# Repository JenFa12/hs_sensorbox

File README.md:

# hs_sensorbox
This is a sensorbox for home assistant

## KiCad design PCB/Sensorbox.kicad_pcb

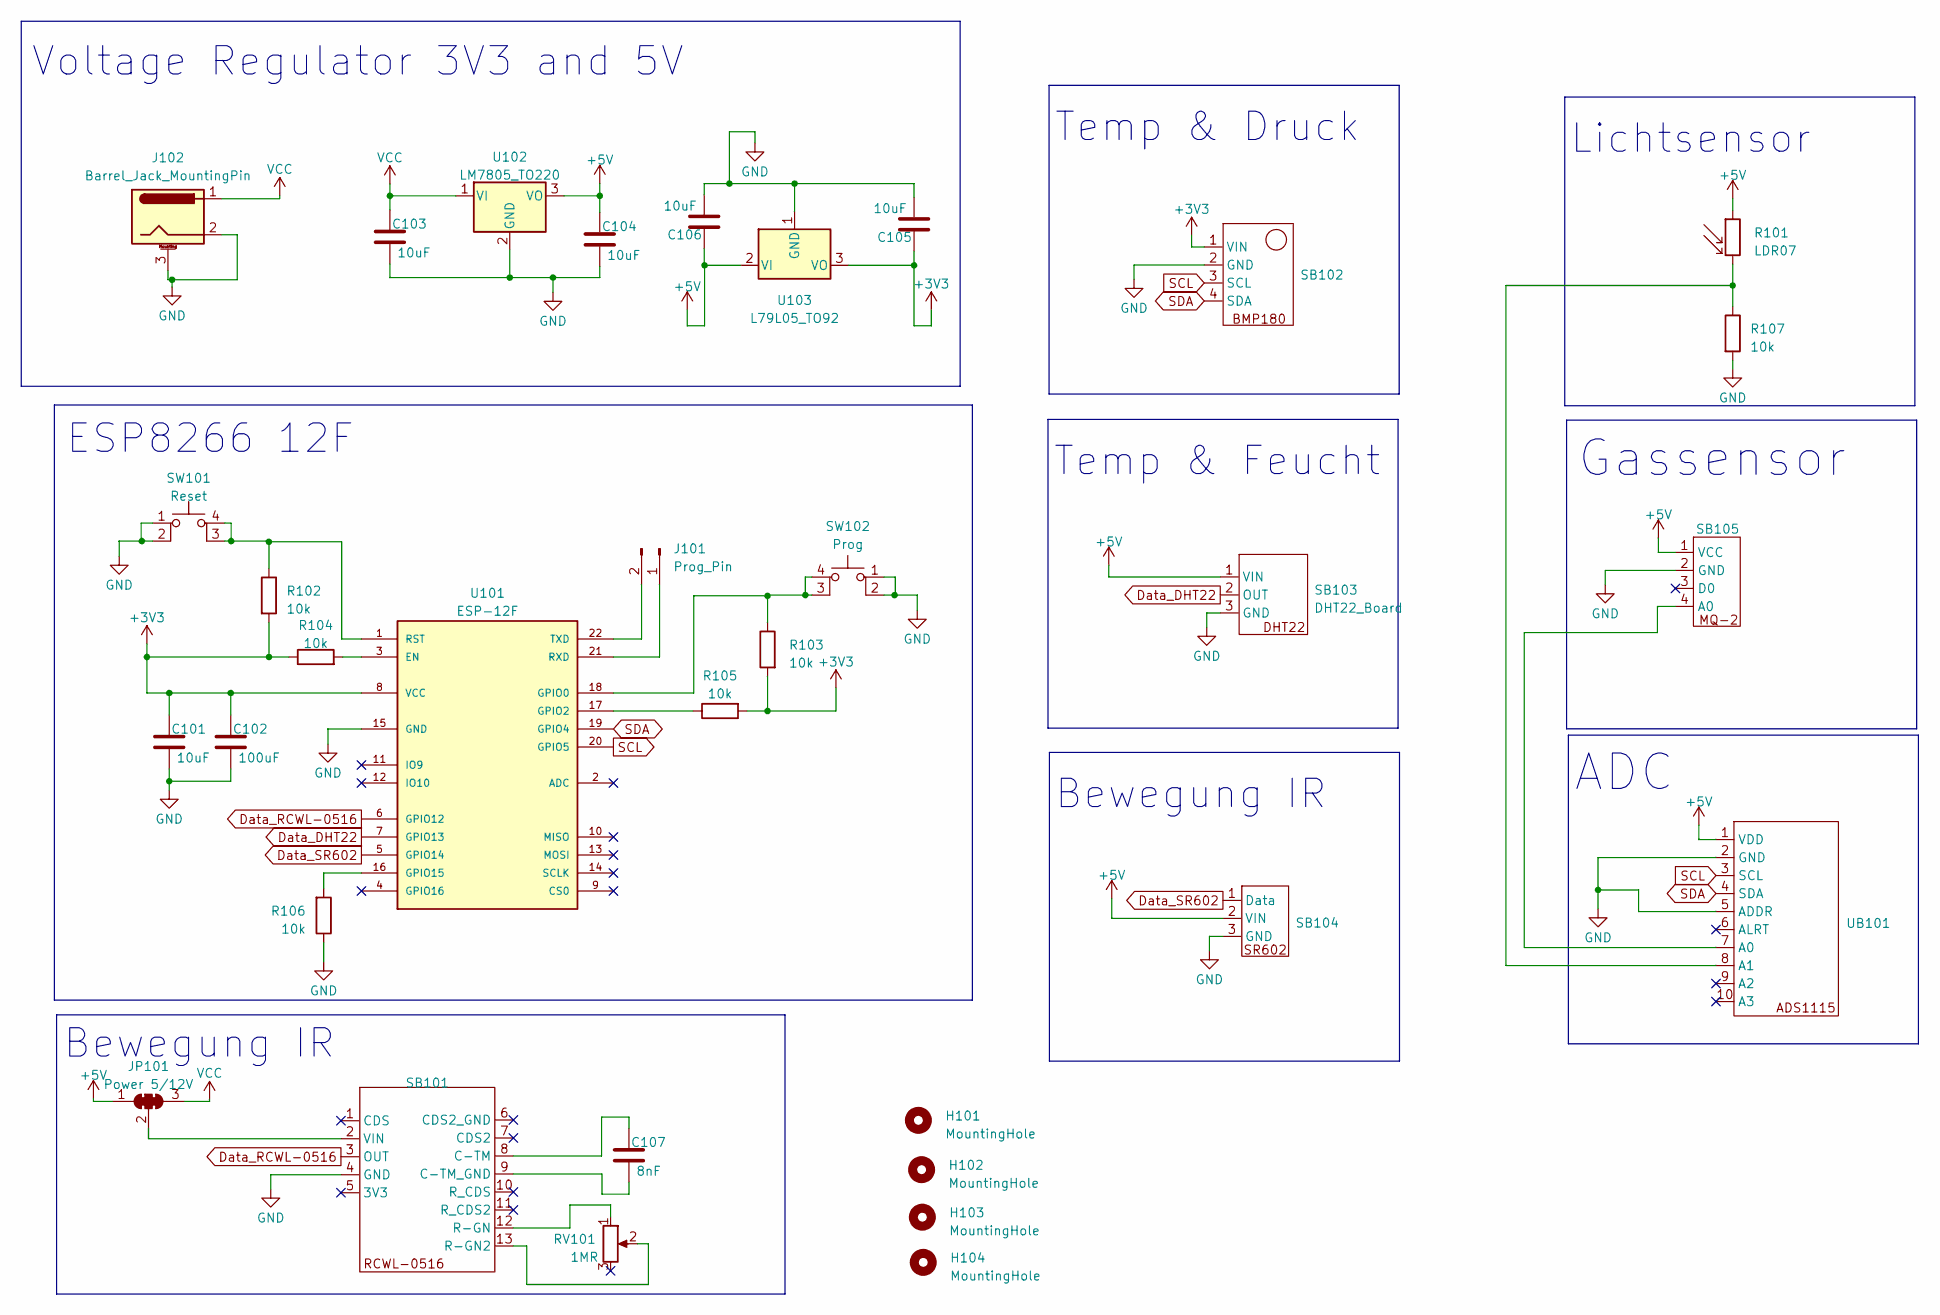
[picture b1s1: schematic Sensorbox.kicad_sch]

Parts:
C101, C103, C104, C105, C106: 10uF; C_0805_2012Metric_Pad1.18x1.45mm_HandSolder
C102: 100uF; C_0805_2012Metric_Pad1.18x1.45mm_HandSolder
C107: 8nF; C_0805_2012Metric_Pad1.18x1.45mm_HandSolder
H101, H102, H103, H104: MountingHole; MountingHole_3.2mm_M3
J101: Prog_Pin; PinHeader_1x02_P1.27mm_Vertical
J102: Barrel_Jack_MountingPin; BarrelJack_GCT_DCJ200-10-A_Horizontal
JP101: Power 5/12V; SolderJumper-3_P1.3mm_Open_RoundedPad1.0x1.5mm_NumberLabels
R101: LDR07; R_LDR_5.1x4.3mm_P3.4mm_Vertical
R102, R103, R104, R105, R106, R107: 10k; R_0805_2012Metric_Pad1.20x1.40mm_HandSolder
RV101: 1MR; Potentiometer_Bourns_3386F_Vertical
SB101: RCWL-0516
SB102: BMP180
SB103: DHT22_Board; DHT22-horizontal
SB104: SR602_Board
SB105: MQ-2
SW101: Reset; Button
SW102: Prog; Button
U101: ESP-12F
U102: LM7805_TO220; TO-220-3_Vertical
U103: L79L05_TO92; TO-92_Inline
UB101: ADC1115_Board

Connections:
+3V3: C101.1, C102.1, C105.1, R102.2, R103.2, R104.1, R105.2, SB102.1 (VIN), U101.8 (VCC), U103.3 (VO)
+5V: C104.1, C106.1, JP101.1 (A), R101.1, SB103.1 (VIN), SB104.2 (VIN), SB105.1 (VCC), U102.3 (VO), U103.2 (VI), UB101.1 (VDD)
Data_DHT22: SB103.2 (OUT), U101.7 (GPIO13)
Data_RCWL-0516: SB101.3 (OUT), U101.6 (GPIO12)
Data_SR602: SB104.1 (Data), U101.5 (GPIO14)
GND: C101.2, C102.2, C103.2, C104.2, C105.2, C106.2, J102.2, J102.3 (MountPin), R106.1, R107.2, SB101.4 (GND), SB102.2 (GND), SB103.3 (GND), SB104.3 (GND), SB105.2 (GND), SW101.1, SW101.2, SW102.1, SW102.2, U101.15 (GND), U102.2 (GND), U103.1 (GND), UB101.2 (GND), UB101.5 (ADDR)
unnamed: J101.1, U101.21 (RXD)
unnamed: J101.2, U101.22 (TXD)
unnamed: JP101.2 (C), SB101.2 (VIN)
unnamed: C107.1, SB101.8 (C-TM)
unnamed: C107.2, SB101.9 (C-TM_GND)
unnamed: RV101.2, SB101.13 (R-GN2)
unnamed: RV101.1, SB101.12 (R-GN)
unnamed: SB105.4 (A0), UB101.7 (A0)
unnamed: R102.1, SW101.3 (K), SW101.4 (A), U101.1 (RST)
unnamed: R103.1, SW102.3 (K), SW102.4 (A), U101.18 (GPIO0)
unnamed: R104.2, U101.3 (EN)
unnamed: R105.1, U101.17 (GPIO2)
unnamed: R106.2, U101.16 (GPIO15)
unnamed: R101.2, R107.1, UB101.8 (A1)
SCL: SB102.3 (SCL), U101.20 (GPIO5), UB101.3 (SCL)
SDA: SB102.4 (SDA), U101.19 (GPIO4), UB101.4 (SDA)
VCC: C103.1, J102.1, JP101.3 (B), U102.1 (VI)

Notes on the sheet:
ESP8266 12F
Lichtsensor
Temp & Druck
Voltage Regulator 3V3 and 5V
ADC
Bewegung IR
Temp & Feucht
Gassensor

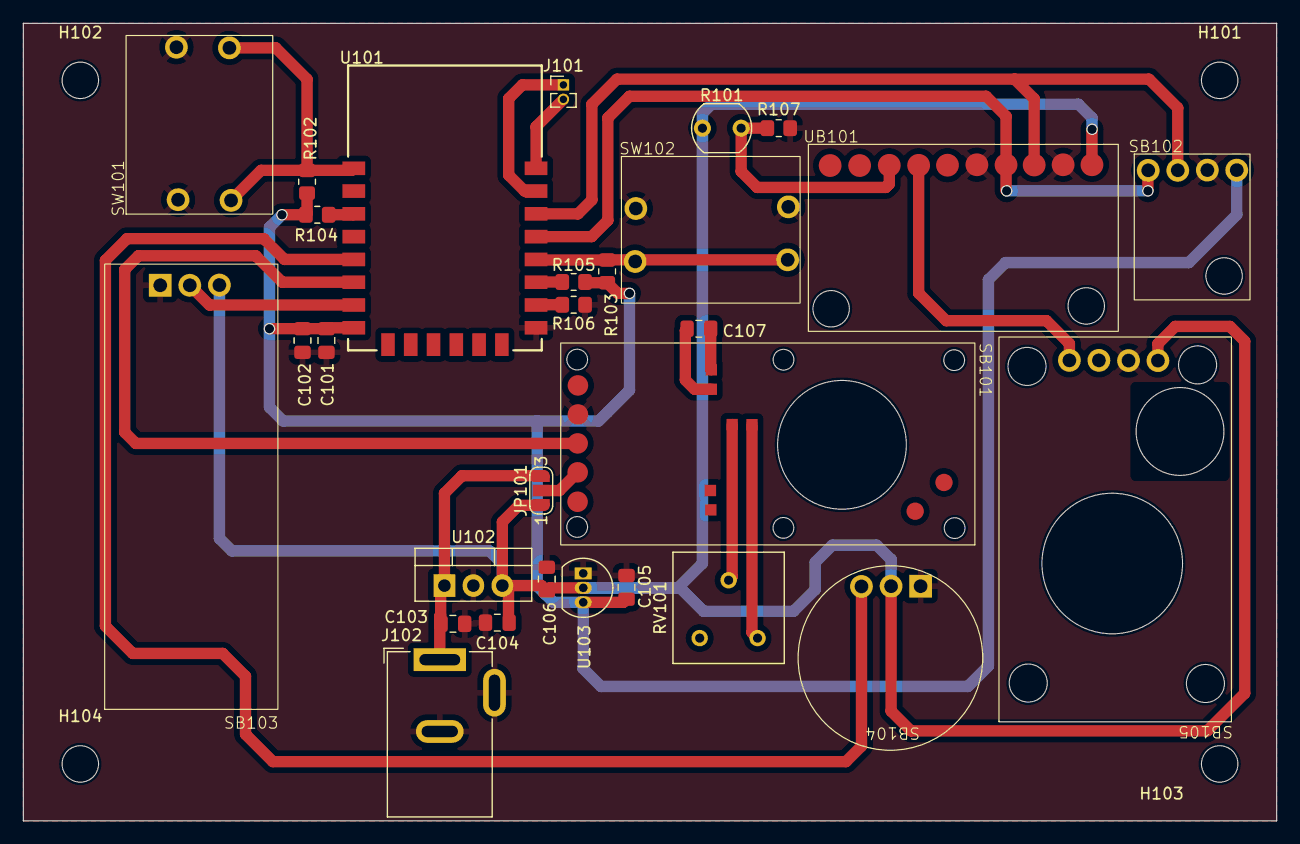
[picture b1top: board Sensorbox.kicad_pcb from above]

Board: 2 copper layers, 110.0 x 70.0 mm, 33 parts (0 on the bottom side), 23 nets.

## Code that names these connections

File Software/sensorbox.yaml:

esphome:
  name: sensorbox
  friendly_name: Sensorbox

esp8266:
  board: esp12e

# Enable logging
logger:

# Enable Home Assistant API
api:
  encryption:
    key: "" # Use your own key

ota:
  password: "" # Use your own ota password

wifi:
  ssid: !secret wifi_ssid
  password: !secret wifi_password

  # Enable fallback hotspot (captive portal) in case wifi connection fails
  ap:
    ssid: "Sensorbox Fallback Hotspot"
    password: "" # Use your own password

captive_portal:

# I2C Configuration for BMP180 and ADS1115
i2c:
  sda: GPIO4
  scl: GPIO5
  scan: True

number:
  - platform: template
    name: "Präsenzsensor Ein-Verzögerung"
    id: praesenzsensor_delay_on
    min_value: 1
    max_value: 60
    step: 1
    initial_value: 1
    optimistic: true

  - platform: template
    name: "Präsenzsensor Aus-Verzögerung"
    id: praesenzsensor_delay_off
    min_value: 1
    max_value: 300
    step: 1
    initial_value: 160
    optimistic: true

binary_sensor:
  - platform: gpio
    device_class: motion
    pin:
      number: GPIO14
      mode: INPUT_PULLUP
    name: "Bewegungssensor"
      

  - platform: gpio
    device_class: motion
    pin:
      number: GPIO12
      mode: INPUT_PULLUP
    name: "Präsenzmelder"
    filters:
      - delayed_on: !lambda "return id(praesenzsensor_delay_on).state * 1000;"
      - delayed_off: !lambda "return id(praesenzsensor_delay_off).state * 1000;"

ads1115:
  - address: 0x48

sensor:
  - platform: ads1115
    multiplexer: 'A0_GND'
    gain: 2.048
    resolution: 16_BITS
    name: "MQ-2 Gassensor"
    id: mq_adc
    device_class: gas
    filters:
      - offset: 0.2248
      - multiply: 100
    unit_of_measurement: "%"
    update_interval: 1s
  
  - platform: ads1115
    multiplexer: 'A1_GND'
    gain: 6.144
    resolution: 16_BITS
    name: "LDR Wert"
    id: ldr_adc
    filters:
      - lambda: "return (((x / 4095.0) * 6.144 * 1000.0) / (pow((1.0 - (x / 4095.0)), 0.8) * 5.0)*1000);"
    unit_of_measurement: "Lux"
    update_interval: 4s

  - platform: bmp085
    temperature:
      name: "BMP180 Temperature"
      id: "bmp085_temperature"
    pressure:
      name: "BMP180 Pressure"
    update_interval: 10s
  
  - platform: dht
    pin: GPIO13 
    model: DHT11
    temperature:
      name: "DHT11 Temperatur"
      id: "dht11_temperature"
    humidity:
      name: "DHT11 Luftfeuchtigkeit"
    update_interval: 10s

  - platform: template
    name: "Durchschnittstemperatur"
    unit_of_measurement: "°C"
    device_class: temperature
    accuracy_decimals: 1
    lambda: |-
      return (id(dht11_temperature).state + id(bmp085_temperature).state) / 2.0;
    update_interval: 10s
    

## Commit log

2024-01-17 added esp code and pcb
2024-01-25 added drill files
2024-01-25 'Changed speed for the drill files
2024-01-27 alignmnent holes 5mm
2024-02-05 added hightmap
2024-02-05 added iso routing
2024-02-05 added ncc for front plate
2024-02-05 changed offset from ncc file
2024-02-06 added in board cutouts
2024-02-06 chenget cut depth from 1 to multi depth
2024-02-06 changed depth
2024-02-06 cutout for poti
2024-02-06 added back trace
2024-02-06 added back trace2
2024-02-17 deleted all FlatCam files
2024-02-19 added FlatCam Files
2024-02-21 added new ncc file for front
2024-02-21 added iso and ncc für back side
